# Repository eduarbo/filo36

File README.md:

# Flan36

**36 keys. Piantor angles. Your keycaps, your frames.**

**[Explore and customize in 3D →](https://eduarbo.github.io/flan36/)** · **[Parts and buying links →](docs/parts.md)** · **[Edit in FreeCAD →](docs/freecad.md)**

*RevI: key-aligned local curves, three interchangeable cases, optional exposed display stack, magnetic frames and one cradle for two battery sizes. Physical fit untested.*

**[Themes and print kits](docs/themes-printing.md)** — Sixteen coordinated themes, personal keycap palettes, linked rim/frame colors and selected STL/3MF parts.

**[Case variants](docs/cases.md)** — Solid, Color rim and Terrace; actual meshes in the explorer.

Flan36 is a low-profile wireless split keyboard in development by [Eduardo Ruiz](https://github.com/eduarbo). It keeps Piantor’s key centers and angles, with five columns and three thumb keys per half.

- **KLP Lamé choices:** all 38 Choc-stem variants catalogued; 28 qualify in at least one position. The viewer checks complete combinations and exports a configuration for FreeCAD.
- **Magnetic frames:** Cartridge, Arcade, Mecha, Kintsugi, Handheld, Retro TV and Cyberpunk, with multicolor relief palettes, plus three plain styles and separate body colors per half. Opaque skirts hide the stack; the display has its own support.
- **Keycap colors:** paint all keys, rows, columns or individual keys; save and share your own palettes.
- **Free tools:** KiCad for electronics, FreeCAD for the case, StepUp for exchange. Editable source, STEP/STL, offline viewer and GLB included.
- **Intended hardware:** Choc v1 hot-swap, two nice!nano controllers and two nice!view displays. One display remains the fallback.

**Status: digital prototype, not ready to manufacture.** Both PCB studies have zero geometric DRC violations and 104 unconnected items each. Routing, exact connectors, printed retention, BLE and power consumption still require work. The visual model does not establish hardware compatibility.

**[Keycaps and frames](docs/customize.md) · [Design](docs/design.md) · [Build](docs/build.md) · [CAD files](docs/cad.md) · [Progress](docs/progress.md)**

Based on [Piantor by beekeeb](https://github.com/beekeeb/piantor), with [KLP Lamé by braindefender](https://github.com/braindefender/KLP-Lame-Keycaps). [Credits and licenses](ATTRIBUTION.md). [Contributing](CONTRIBUTING.md).

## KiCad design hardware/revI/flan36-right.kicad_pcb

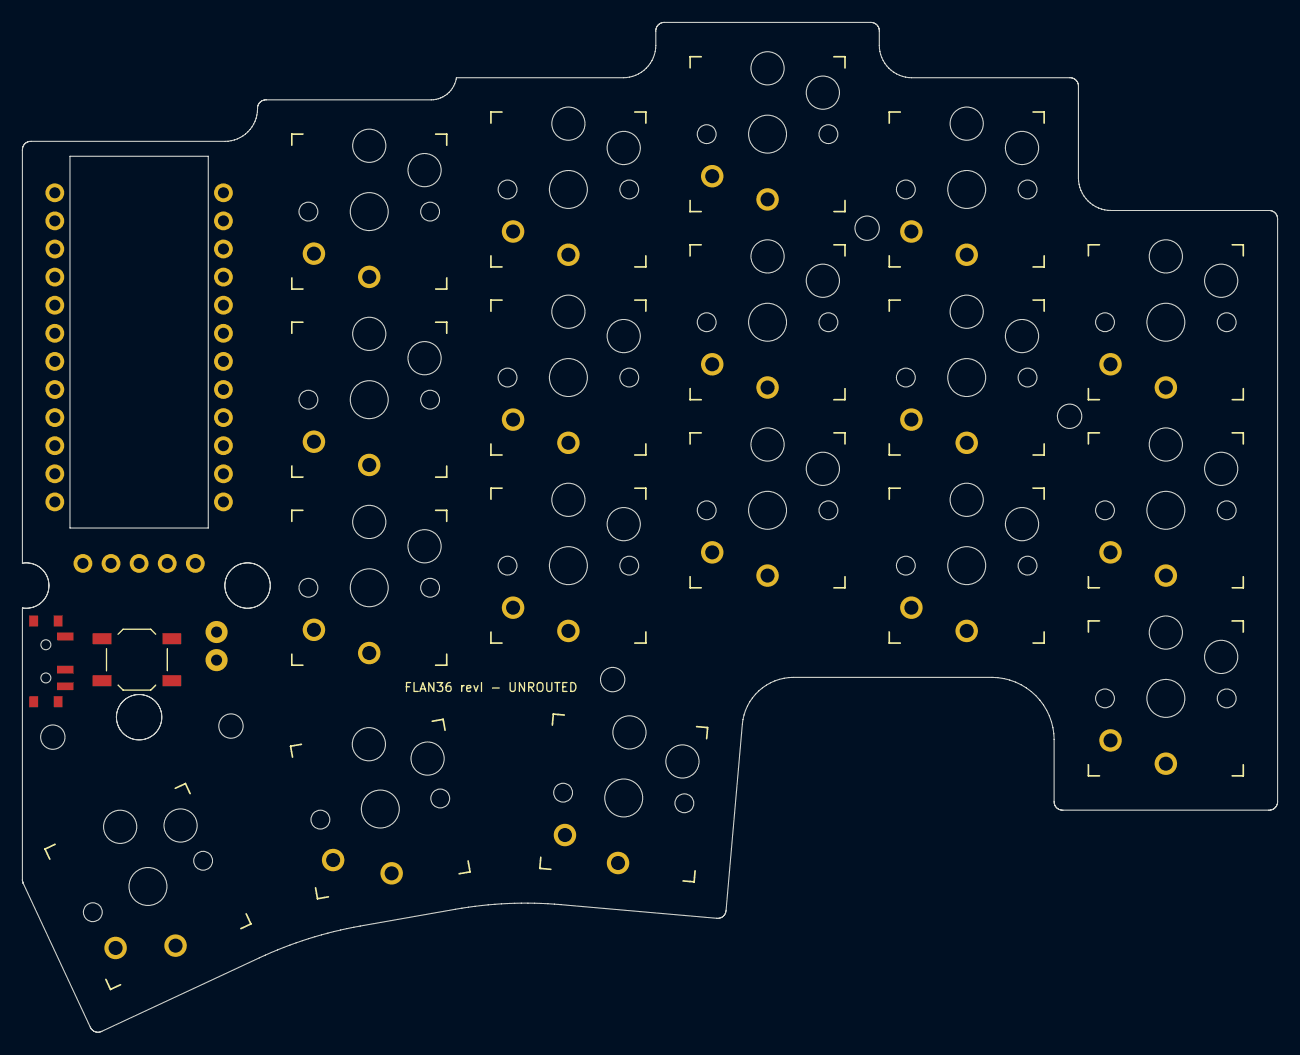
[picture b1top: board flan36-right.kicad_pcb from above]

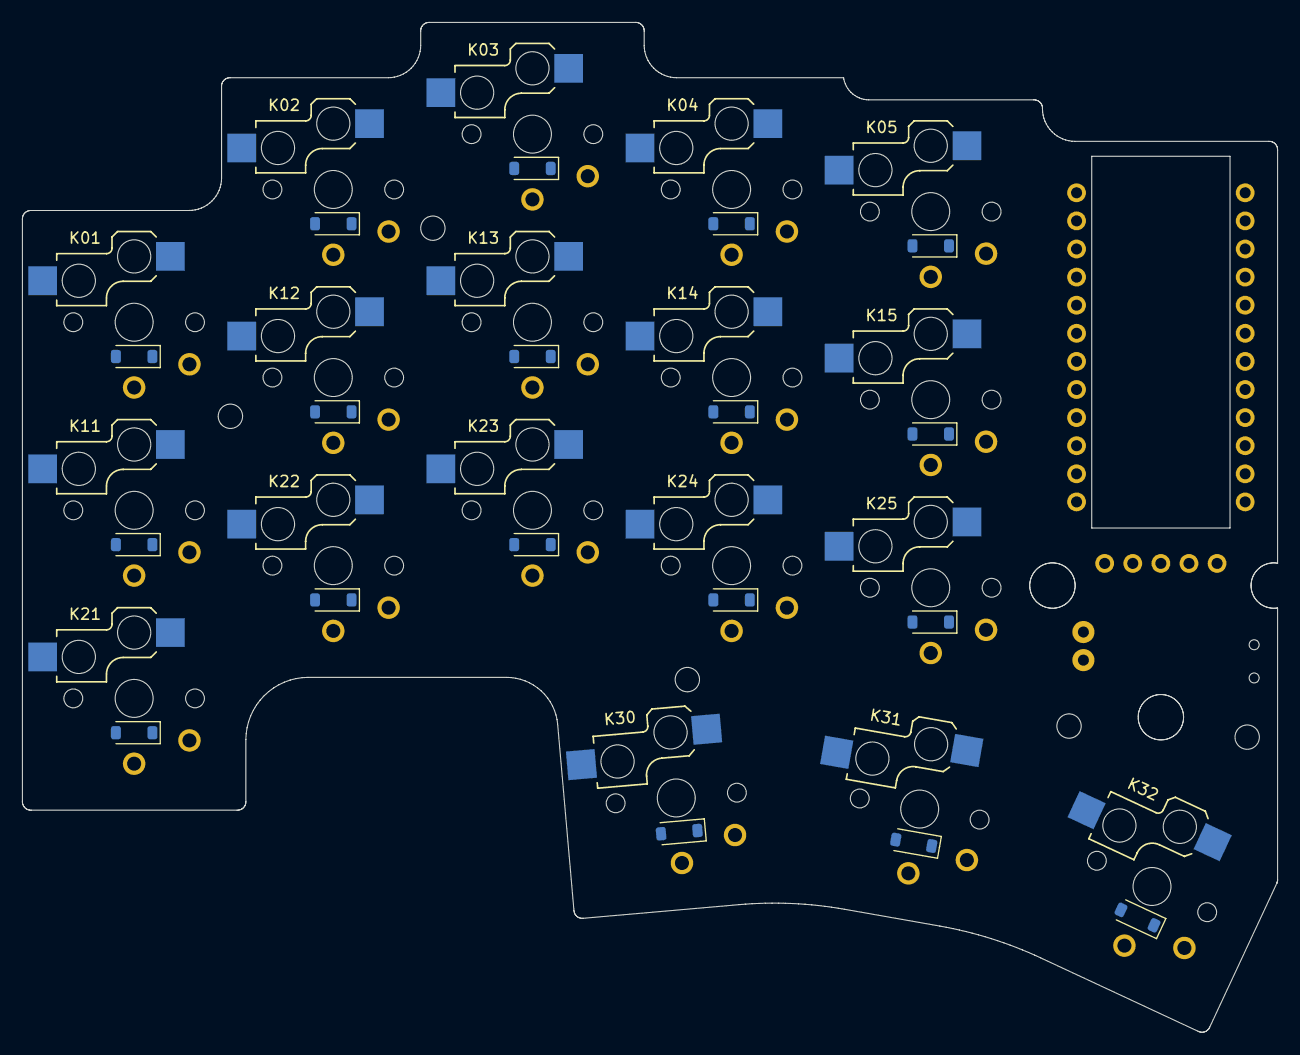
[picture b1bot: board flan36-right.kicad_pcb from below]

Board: 2 copper layers, 113.4 x 91.3 mm, 46 parts (18 on the bottom side), 36 nets, no tracks yet.

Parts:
D01, D02, D03, D04, D05, D11, D12, D13, D14, D15, D21, D22, D23, D24, D25, D30, D31, D32: D_SOD-123
H1, H2, H3, H4, H5: MountingHole_2.2mm_M2
J1: BATTERY_PIGTAIL; Battery_pigtail_2.54
J2: nice!view; nice_view_5pin
K01, K02, K03, K04, K05, K11, K12, K13, K14, K15, K21, K22, K23, K24, K25, K30, K31, K32: KEYSW; Kailh_socket_PG1350_optional
SW1: SW_SPDT_PCM12
SW2: SW_SPST_TL3342
U1: nice!nano v2; nice_nano_v2_standard_edge

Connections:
BAT_PLUS: J1.1, SW1.1
BAT_SW: SW1.2, U1.RAW
COL0: K30.1, U1.D6
COL1: K01.1, K11.1, K21.1, K31.1, U1.D7
COL2: K02.1, K12.1, K22.1, K32.1, U1.D8
COL3: K03.1, K13.1, K23.1, U1.D9
COL4: K04.1, K14.1, K24.1, U1.D10
COL5: K05.1, K15.1, K25.1, U1.D16
DISP_CS: J2.5, U1.D14
DISP_MOSI: J2.1, U1.D1
DISP_SCK: J2.2, U1.D0
GND: J1.2, J2.4, SW2.2, U1.GND1, U1.GND2, U1.GND3
K01_A: D01.2, K01.2
K02_A: D02.2, K02.2
K03_A: D03.2, K03.2
K04_A: D04.2, K04.2
K05_A: D05.2, K05.2
K11_A: D11.2, K11.2
K12_A: D12.2, K12.2
K13_A: D13.2, K13.2
K14_A: D14.2, K14.2
K15_A: D15.2, K15.2
K21_A: D21.2, K21.2
K22_A: D22.2, K22.2
K23_A: D23.2, K23.2
K24_A: D24.2, K24.2
K25_A: D25.2, K25.2
K30_A: D30.2, K30.2
K31_A: D31.2, K31.2
K32_A: D32.2, K32.2
RESET: SW2.1, U1.RST
ROW0: D01.1, D02.1, D03.1, D04.1, D05.1, U1.D2
ROW1: D11.1, D12.1, D13.1, D14.1, D15.1, U1.D3
ROW2: D21.1, D22.1, D23.1, D24.1, D25.1, U1.D4
ROW3: D30.1, D31.1, D32.1, U1.D5
VCC: J2.3, U1.VCC
